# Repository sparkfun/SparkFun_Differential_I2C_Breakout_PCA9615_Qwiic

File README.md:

SparkFun Differential I2C Breakout - PCA9615 (Qwiic)
========================================

[*SparkFun Differential I2C Breakout - PCA9615 (Qwiic) (BOB-14589)*](https://www.sparkfun.com/products/14589)

The SparkFun Differential I<sup>2</sup>C Breakout is the fastest and easiest way to extend the range of your I<sup>2</sup>C communication bus. The breakout uses NXP’s PCA9615 IC, which converts the two default I<sup>2</sup>C signals into four differential signals, two for SCL and two for SDA. 

Repository Contents
-------------------

* **/Documentation** - Datasheets, additional product information
* **/Hardware** - Eagle design files (.brd, .sch)
* **/Production** - Production panel files (.brd)

Documentation
--------------
* **[Hookup Guide](https://learn.sparkfun.com/tutorials/qwiic-differential-i2c-bus-extender-pca9615-hookup-guide)** - Basic hookup guide for the SparkFun Differential I2C Breakout - PCA9615 (Qwiic).

Product Versions
----------------
* [BOB-14589](https://www.sparkfun.com/products/14589)

License Information
-------------------

This product is _**open source**_! 

Please review the LICENSE.md file for license information. 

If you have any questions or concerns on licensing, please contact techsupport@sparkfun.com.

Distributed as-is; no warranty is given.

- Your friends at SparkFun.

_<COLLABORATION CREDIT>_

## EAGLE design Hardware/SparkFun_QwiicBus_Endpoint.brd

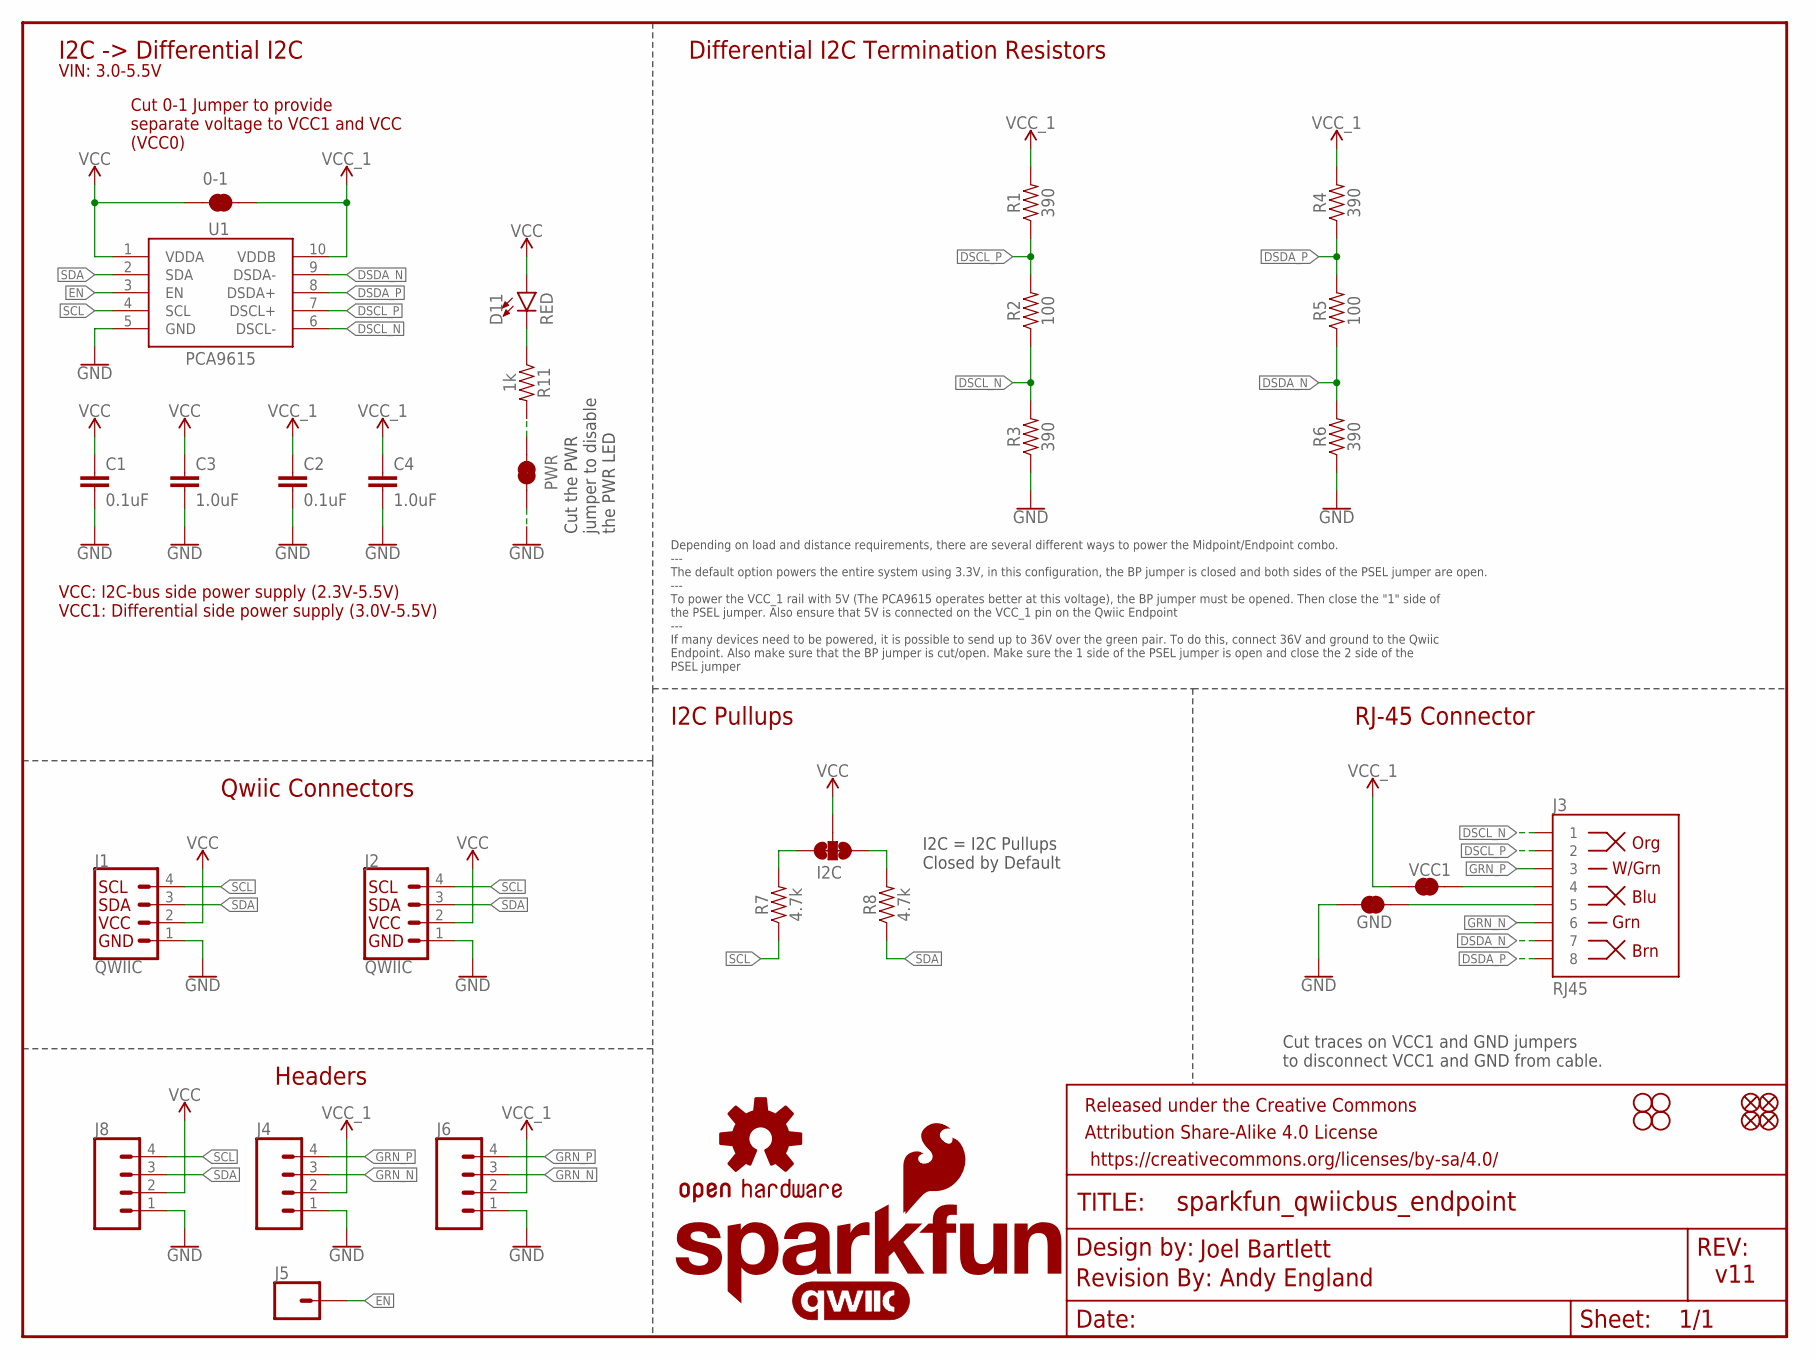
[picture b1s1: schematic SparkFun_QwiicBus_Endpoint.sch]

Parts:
0-1: JUMPER-SMT_2_NC_TRACE_SILK; SMT-JUMPER_2_NC_TRACE_SILK
C1, C2: 0.1uF; 0603
C3, C4: 1.0uF; 0603
D11: RED; LED-0603
FD1, FD2, FD3, FD4: FIDUCIALUFIDUCIAL; FIDUCIAL-MICRO
FRAME1: FRAME-LETTER; CREATIVE_COMMONS
GND: JUMPER-SMT_2_NC_TRACE_SILK; SMT-JUMPER_2_NC_TRACE_SILK
H1, H2, H3, H4: STAND-OFF
I2C: JUMPER-SMT_3_2-NC_TRACE_SILK; SMT-JUMPER_3_2-NC_TRACE_SILK
J1, J2: QWIIC; JST04_1MM_RA
J3: RJ45; RJ45-8
J4, J6, J8: CONN_041X04_NO_SILK; 1X04_NO_SILK
J5: CONN_01PTH_NO_SILK_YES_STOP; 1X01_NO_SILK
LOGO1: OSHW-LOGOM; OSHW-LOGO-M
LOGO2: REVISION
LOGO3: QWIIC_LOGO_4MM; QWIIC_4MM
LOGO4: SFE_LOGO_NAME_FLAME.1_INCH; SFE_LOGO_NAME_FLAME_.1
LOGO5: SFE_LOGO_FLAME.1_INCH; SFE_LOGO_FLAME_.1
PWR: JUMPER-SMT_2_NC_TRACE_SILK; SMT-JUMPER_2_NC_TRACE_SILK
R1, R3, R4, R6: 390; 0603
R2, R5: 100; 0603
R7, R8: 4.7k; 0603
R11: 1k; 0603
U1: PCA9615; TSSOP10
VCC1: JUMPER-SMT_2_NC_TRACE_SILK; SMT-JUMPER_2_NC_TRACE_SILK

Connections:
DSCL_N: J3.1, R2.1, R3.2, U1.6 (DSCL-)
DSCL_P: J3.2, R1.1, R2.2, U1.7 (DSCL+)
DSDA_N: J3.7, R5.1, R6.2, U1.9 (DSDA-)
DSDA_P: J3.8, R4.1, R5.2, U1.8 (DSDA+)
EN: J5.1, U1.3 (EN)
GND: C1.2, C2.2, C3.2, C4.2, GND.1, J1.1, J2.1, J4.1, J6.1, J8.1, PWR.1, R3.1, R6.1, U1.5 (GND)
GRN_N: J3.6, J4.3, J6.3
GRN_P: J3.3, J4.4, J6.4
unnamed: J3.4, VCC1.2
unnamed: GND.2, J3.5
unnamed: I2C.1, R8.2
unnamed: I2C.3, R7.2
unnamed: D11.C, R11.1
unnamed: PWR.2, R11.2
SCL: J1.4, J2.4, J8.4, R7.1, U1.4 (SCL)
SDA: J1.3, J2.3, J8.3, R8.1, U1.2 (SDA)
VCC: 0-1.2, C1.1, C3.1, D11.A, I2C.2, J1.2, J2.2, J8.2, U1.1 (VDDA)
VCC_1: 0-1.1, C2.1, C4.1, J4.2, J6.2, R1.2, R4.2, U1.10 (VDDB), VCC1.1

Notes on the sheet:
Joel Bartlett
I2C -> Differential I2C
Qwiic Connectors
v11
I2C = I2C Pullups Closed by Default
Headers
I2C Pullups
RJ-45 Connector
Differential I2C Termination Resistors
Cut traces on VCC1 and GND jumpers to disconnect VCC1 and GND from cable.
Andy England
Cut the PWR jumper to disable the PWR LED
VIN: 3.0-5.5V
VCC: I2C-bus side power supply (2.3V-5.5V) VCC1: Differential side power supply (3.0V-5.5V)
Cut 0-1 Jumper to provide separate voltage to VCC1 and VCC (VCC0)
Depending on load and distance requirements, there are several different ways to power the Midpoint/Endpoint combo. --- The default option powers the entire system using 3.3V, in this configuration, the BP jumper is closed and both sides of the PSEL jumper are open. --- To power the VCC_1 rail with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

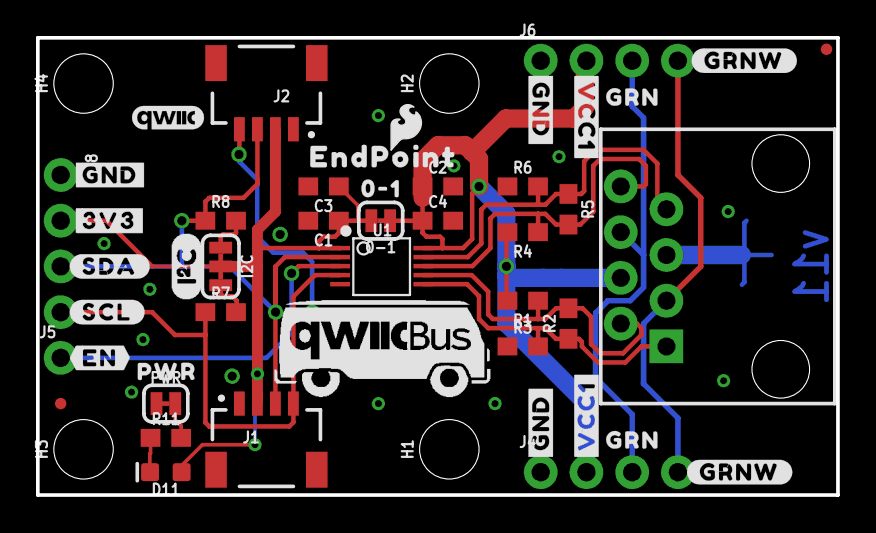
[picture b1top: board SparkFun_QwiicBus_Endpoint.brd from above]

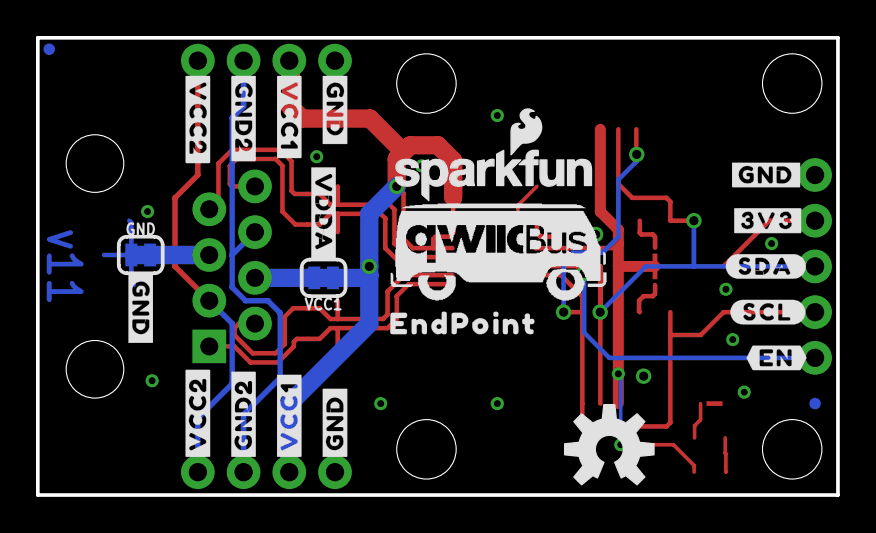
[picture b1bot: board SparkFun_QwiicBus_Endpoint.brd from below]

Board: 2 copper layers, 44.5 x 25.4 mm, 76 parts (23 on the bottom side), 18 nets.

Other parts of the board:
U$1: I2C
U$2, U$29: GRN0
U$3, U$4, U$5, U$6, U$13, U$33, U$34: #GND#0
U$7, U$8: #3V3#0
U$9, U$15: #SDA#0
U$10, U$16: #SCL#0
U$11, U$17: #EN#0
U$12: #VDDA#0
U$14, U$18: #GND2#0
U$19, U$22: #GRNW#0
U$20, U$21, U$31, U$32: #VCC1#0
U$23, U$28: QWIICBUS#WORKING#LOGO#JPG
U$24, U$30: #VCC2#0
U$25: 0#10
U$26, U$35: ENDPOINT0
U$27: PWR0

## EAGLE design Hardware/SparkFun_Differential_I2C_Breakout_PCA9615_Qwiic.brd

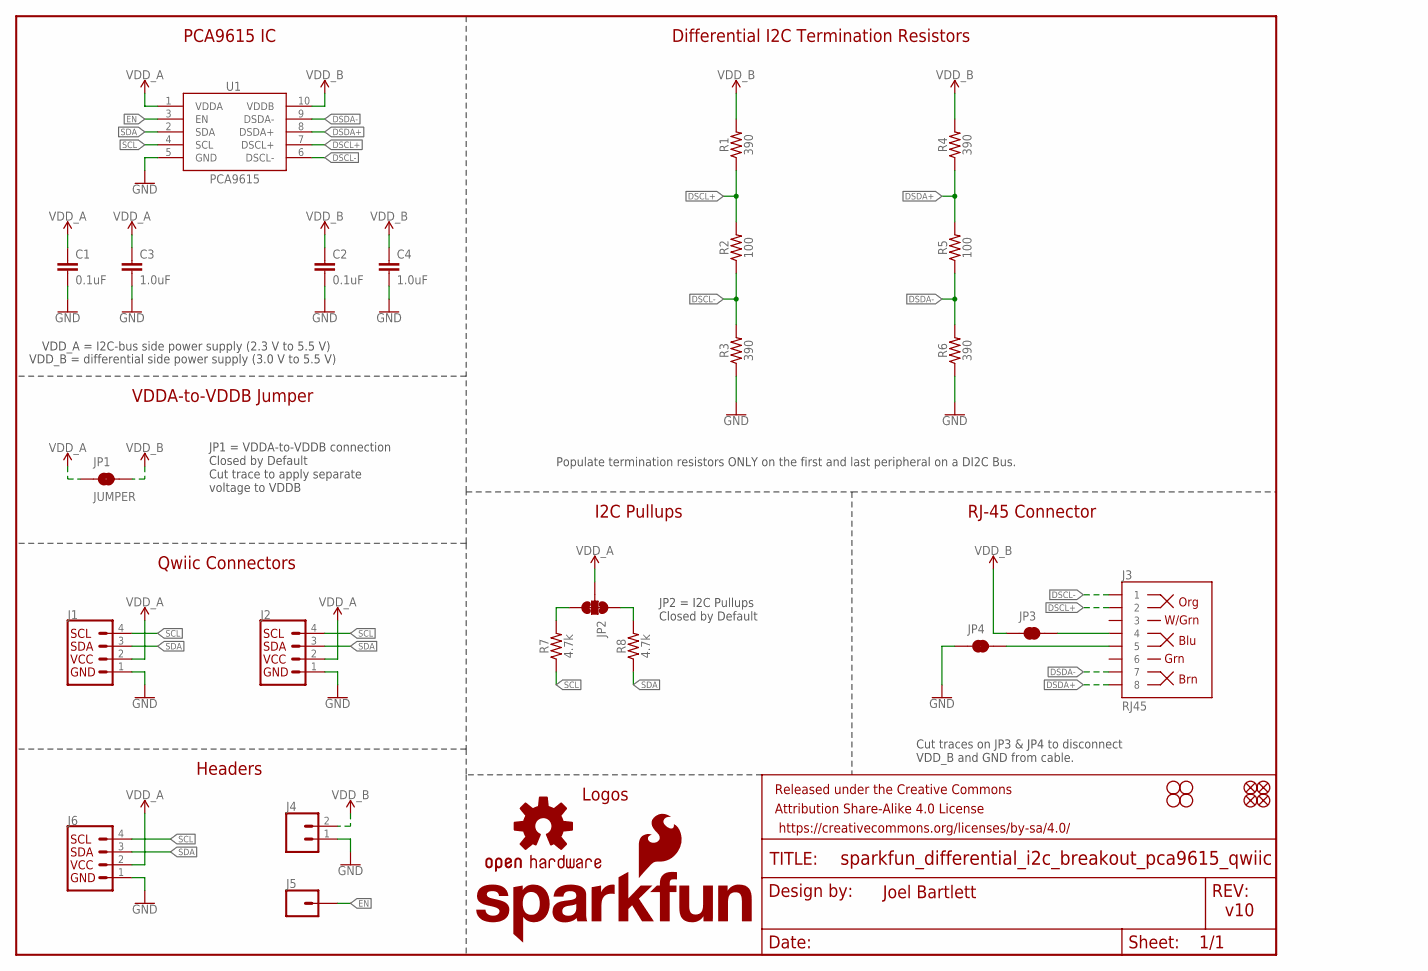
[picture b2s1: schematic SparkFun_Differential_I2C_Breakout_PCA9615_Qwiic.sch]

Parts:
C1, C2: 0.1uF; 0603
C3, C4: 1.0uF; 0603
FD1, FD2, FD3, FD4: FIDUCIALUFIDUCIAL; FIDUCIAL-MICRO
FRAME1: FRAME-LETTER; CREATIVE_COMMONS
H1, H2, H3, H4: STAND-OFF
J1, J2: QWIIC_CONNECTORJS-1MM; 1X04_1MM_RA
J3: RJ45; RJ45-8
J4: CONN_021X02_NO_SILK; 1X02_NO_SILK
J5: CONN_01PTH_NO_SILK_YES_STOP; 1X01_NO_SILK
J6: I2C_STANDARD_NO_SILK; 1X04_NO_SILK
JP1: JUMPER; SMT-JUMPER_2_NC_TRACE_SILK
JP2: JUMPER-SMT_3_2-NC_TRACE_SILK; SMT-JUMPER_3_2-NC_TRACE_SILK
JP3, JP4: JUMPER-SMT_2_NC_TRACE_SILK; SMT-JUMPER_2_NC_TRACE_SILK
LOGO1: OSHW-LOGOM; OSHW-LOGO-M
LOGO5: SFE_LOGO_NAME_FLAME.1_INCH; SFE_LOGO_NAME_FLAME_.1
R1, R3, R4, R6: 390; 0603
R2, R5: 100; 0603
R7, R8: 4.7k; 0603
U1: PCA9615; TSSOP10

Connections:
DSCL+: J3.2, R1.1, R2.2, U1.7 (DSCL+)
DSCL-: J3.1, R2.1, R3.2, U1.6 (DSCL-)
DSDA+: J3.8, R4.1, R5.2, U1.8 (DSDA+)
DSDA-: J3.7, R5.1, R6.2, U1.9 (DSDA-)
EN: J5.1, U1.3 (EN)
GND: C1.2, C2.2, C3.2, C4.2, J1.1, J2.1, J4.1, J6.1 (GND), JP4.1, R3.1, R6.1, U1.5 (GND)
unnamed: J3.4, JP3.2
unnamed: J3.5, JP4.2
unnamed: JP2.1, R8.2
unnamed: JP2.3, R7.2
SCL: J1.4, J2.4, J6.4 (SCL), R7.1, U1.4 (SCL)
SDA: J1.3, J2.3, J6.3 (SDA), R8.1, U1.2 (SDA)
VDD_A: C1.1, C3.1, J1.2, J2.2, J6.2 (VCC), JP1.1, JP2.2, U1.1 (VDDA)
VDD_B: C2.1, C4.1, J4.2, JP1.2, JP3.1, R1.2, R4.2, U1.10 (VDDB)

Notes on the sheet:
Joel Bartlett
VDDA-to-VDDB Jumper
PCA9615 IC
Qwiic Connectors
v10
JP2 = I2C Pullups Closed by Default
Headers
JP1 = VDDA-to-VDDB connection Closed by Default Cut trace to apply separate voltage to VDDB
I2C Pullups
RJ-45 Connector
Logos
Differential I2C Termination Resistors
Populate termination resistors ONLY on the first and last peripheral on a DI2C Bus.
VDD_A = I2C-bus side power supply (2.3 V to 5.5 V)
VDD_B = differential side power supply (3.0 V to 5.5 V)
Cut traces on JP3 & JP4 to disconnect VDD_B and GND from cable.

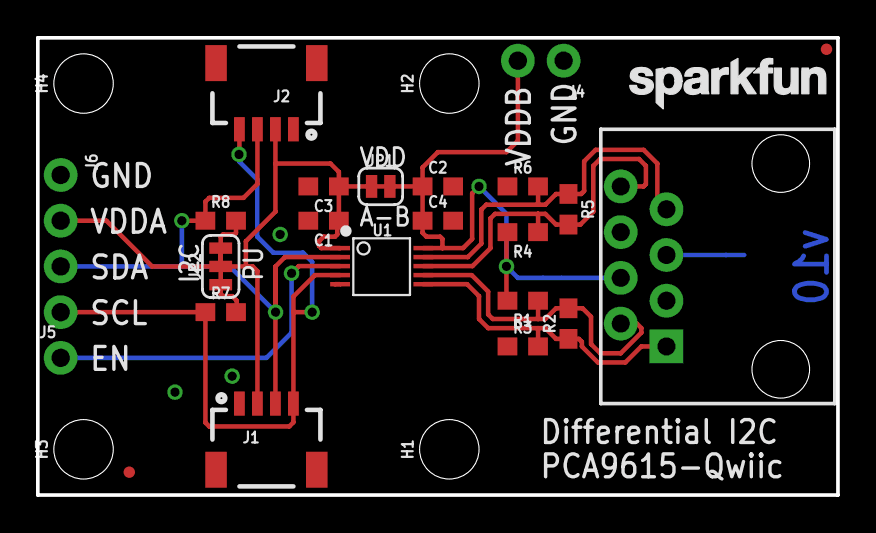
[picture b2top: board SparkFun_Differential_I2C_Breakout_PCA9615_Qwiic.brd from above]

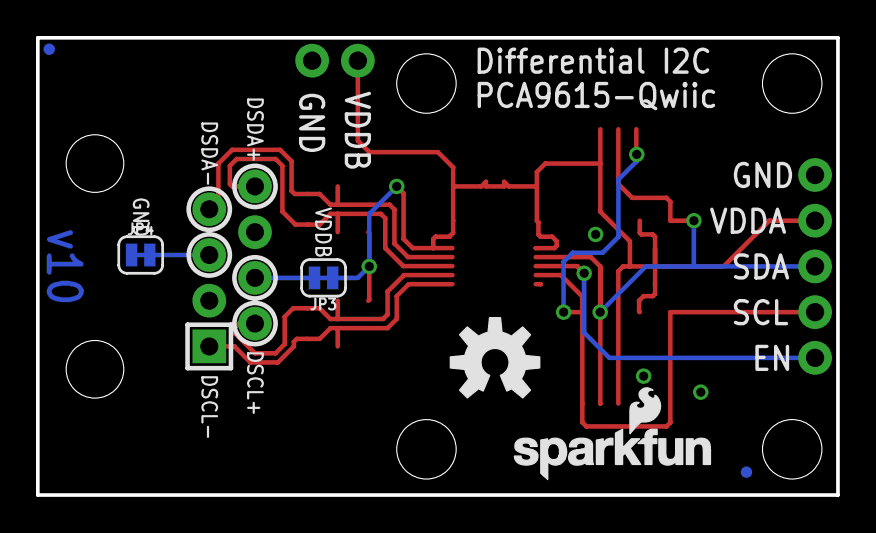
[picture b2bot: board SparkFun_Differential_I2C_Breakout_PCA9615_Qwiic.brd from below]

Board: 2 copper layers, 44.5 x 25.4 mm, 35 parts (6 on the bottom side), 14 nets.

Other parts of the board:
LOGO3: SFE_LOGO_NAME.1_INCH; SFE_LOGO_NAME_.1

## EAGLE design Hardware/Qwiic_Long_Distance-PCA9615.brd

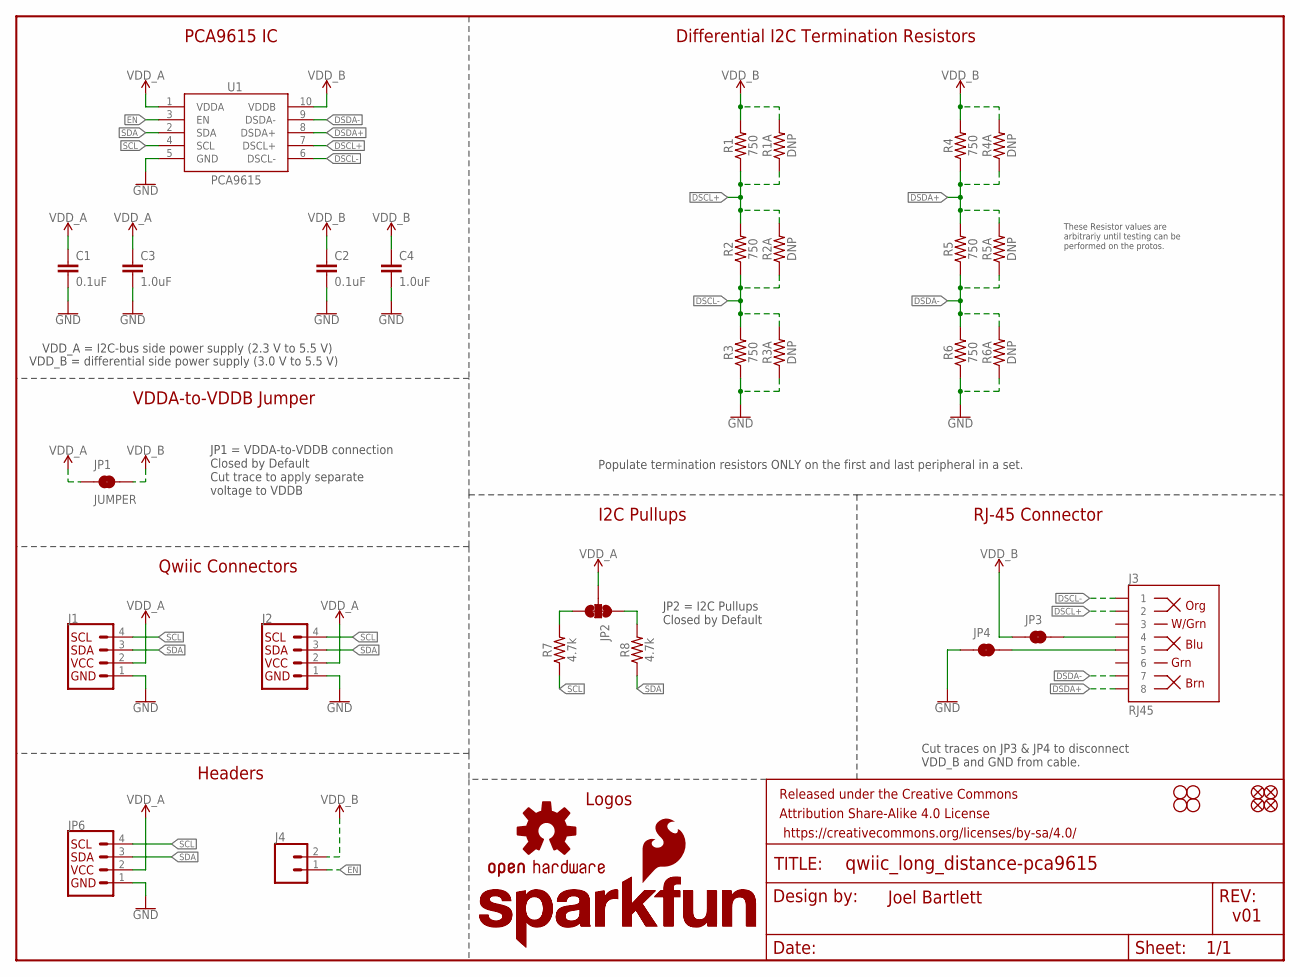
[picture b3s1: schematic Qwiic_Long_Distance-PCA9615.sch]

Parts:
C1, C2: 0.1uF; 0603
C3, C4: 1.0uF; 0603
FD1, FD2, FD3, FD4: FIDUCIALUFIDUCIAL; FIDUCIAL-MICRO
FRAME1: FRAME-LETTER; CREATIVE_COMMONS
H1, H2, H3, H4: STAND-OFF
J1, J2: QWIIC_CONNECTORJS-1MM; 1X04_1MM_RA
J3: RJ45; RJ45-8
J4: CONN_02; 1X02
JP1: JUMPER; SMT-JUMPER_2_NC_TRACE_SILK
JP2: JUMPER-SMT_3_2-NC_TRACE_SILK; SMT-JUMPER_3_2-NC_TRACE_SILK
JP3, JP4: JUMPER-SMT_2_NC_TRACE_SILK; SMT-JUMPER_2_NC_TRACE_SILK
JP6: I2C_STANDARDSILK; 1X04
LOGO1: OSHW-LOGOM; OSHW-LOGO-M
LOGO2: SFE_LOGO_NAME.1_INCH; SFE_LOGO_NAME_.1
LOGO5: SFE_LOGO_NAME_FLAME.1_INCH; SFE_LOGO_NAME_FLAME_.1
R1, R2, R3, R4, R5, R6: 750; 0603
R1A, R2A, R3A, R4A, R5A, R6A: DNP; AXIAL-0.3
R7, R8: 4.7k; 0603
U1: PCA9615; TSSOP10

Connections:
DSCL+: J3.2, R1.1, R1A.P$1 (1), R2.2, R2A.P$2 (2), U1.7 (DSCL+)
DSCL-: J3.1, R2.1, R2A.P$1 (1), R3.2, R3A.P$2 (2), U1.6 (DSCL-)
DSDA+: J3.8, R4.1, R4A.P$1 (1), R5.2, R5A.P$2 (2), U1.8 (DSDA+)
DSDA-: J3.7, R5.1, R5A.P$1 (1), R6.2, R6A.P$2 (2), U1.9 (DSDA-)
EN: J4.1, U1.3 (EN)
GND: C1.2, C2.2, C3.2, C4.2, J1.1, J2.1, JP4.1, JP6.1 (GND), R3.1, R3A.P$1 (1), R6.1, R6A.P$1 (1), U1.5 (GND)
unnamed: J3.4, JP3.2
unnamed: J3.5, JP4.2
unnamed: JP2.1, R8.2
unnamed: JP2.3, R7.2
SCL: J1.4, J2.4, JP6.4 (SCL), R7.1, U1.4 (SCL)
SDA: J1.3, J2.3, JP6.3 (SDA), R8.1, U1.2 (SDA)
VDD_A: C1.1, C3.1, J1.2, J2.2, JP1.1, JP2.2, JP6.2 (VCC), U1.1 (VDDA)
VDD_B: C2.1, C4.1, J4.2, JP1.2, JP3.1, R1.2, R1A.P$2 (2), R4.2, R4A.P$2 (2), U1.10 (VDDB)

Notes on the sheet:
Joel Bartlett
VDDA-to-VDDB Jumper
PCA9615 IC
Qwiic Connectors
v01
JP2 = I2C Pullups Closed by Default
Headers
JP1 = VDDA-to-VDDB connection Closed by Default Cut trace to apply separate voltage to VDDB
I2C Pullups
RJ-45 Connector
Logos
Differential I2C Termination Resistors
Populate termination resistors ONLY on the first and last peripheral in a set.
These Resistor values are arbitrariy until testing can be performed on the protos.
VDD_A = I2C-bus side power supply (2.3 V to 5.5 V)
VDD_B = differential side power supply (3.0 V to 5.5 V)
Cut traces on JP3 & JP4 to disconnect VDD_B and GND from cable.

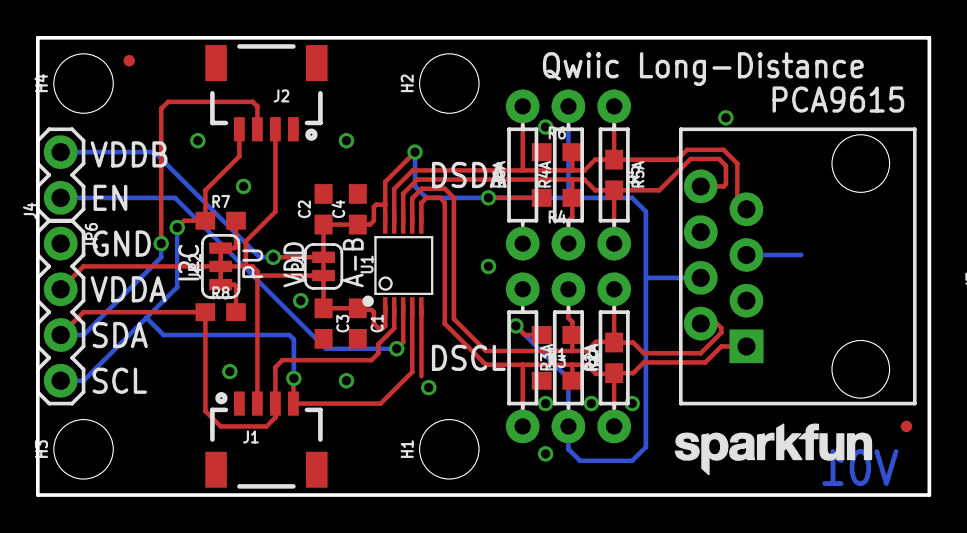
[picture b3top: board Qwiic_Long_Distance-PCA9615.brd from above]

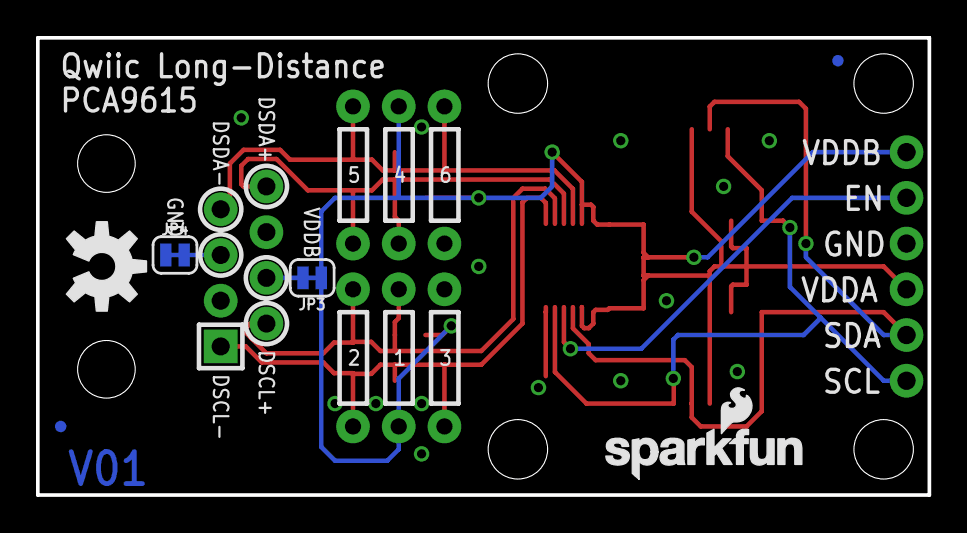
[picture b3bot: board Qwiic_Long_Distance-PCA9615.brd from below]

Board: 2 copper layers, 49.5 x 25.4 mm, 40 parts (6 on the bottom side), 14 nets.

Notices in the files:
parts and their libraries:
SparkFun-Aesthetics: Licensing: CC v3.0 Share-Alike You are welcome to use this library for commercial purposes.
SparkFun-Aesthetics: Released under the Creative Commons Attribution Share-Alike 4.0 License
SparkFun-Aesthetics: https://creativecommons.org/licenses/by-sa/4.0
